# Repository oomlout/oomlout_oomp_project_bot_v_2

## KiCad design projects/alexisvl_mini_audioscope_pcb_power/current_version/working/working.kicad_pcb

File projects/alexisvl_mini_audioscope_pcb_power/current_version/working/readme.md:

# mini_audioscope
 
## summary 
* id: alexisvl_mini_audioscope_pcb_power
* user: alexisvl
* name: mini_audioscope
* board: pcb_power
* repo: https://github.com/alexisvl/mini-audioscope
* src_file_repo_kicad_pcb: pcb-power/pcb-power.kicad_pcb
* src_file_repo_kicad_pcb_link: https://github.com/alexisvl/mini-audioscope/tree/master/pcb-power/pcb-power.kicad_pcb

* src_file_repo_sch: pcb-power/pcb-power.sch
* src_file_repo_sch_link: https://github.com/alexisvl/mini-audioscope/tree/master/pcb-power/pcb-power.sch
* full details link: https://github.com/oomlout/oomlout_oomp_project_bot_v_2/tree/main/projects/alexisvl_mini_audioscope_pcb_power/current_version/working  

## schematic  
  
[schematic (pdf)](working_schematic.pdf) 

## pcb  

[board (pdf)](working.pdf)  

## working_bom
| Id | Designator | Footprint | Quantity | Designation | Supplier and ref |  | None | 
| --- | --- | --- | --- | --- | --- | --- | --- | 
| 1 | R2,R1 | R_Axial_DIN0309_L9.0mm_D3.2mm_P15.24mm_Horizontal | 2 | 330k/Â½W |  |  | [''] | 
| 2 | C11,C23,C24 | CP_Radial_D6.3mm_P2.50mm | 3 | 47u |  |  | [''] | 
| 3 | D10,D2,D4,D6,D3,D11,D7 | D_DO-41_SOD81_P10.16mm_Horizontal | 7 | UF4007 |  |  | [''] | 
| 4 | R8 | R_Axial_DIN0207_L6.3mm_D2.5mm_P10.16mm_Horizontal | 1 | 1k |  |  | [''] | 
| 5 | D12,D13 | D_DO-41_SOD81_P10.16mm_Horizontal | 2 | 1N4004 |  |  | [''] | 
| 6 | D5 | Diode_Bridge_Vishay_GBU | 1 | GBU4J |  |  | [''] | 
| 7 | TP3,TP5 | TestPoint_Loop_D2.60mm_Drill1.4mm_Beaded | 2 | GND |  |  | [''] | 
| 8 | C14,C19 | C_Rect_L26.5mm_W10.5mm_P22.50mm_MKS4 | 2 | 3u3/450 |  |  | [''] | 
| 9 | X14 | Pin_D1.1mm_L8.5mm_W2.5mm_FlatFork | 1 | +400V |  |  | [''] | 
| 10 | U3 | TO-220-3_Vertical | 1 | LM337 |  |  | [''] | 
| 11 | R15,R14 | R_Axial_DIN0309_L9.0mm_D3.2mm_P15.24mm_Horizontal | 2 | 220k/HW |  |  | [''] | 
| 12 | XT1.0 | Pin_D1.1mm_L8.5mm_W2.5mm_FlatFork | 1 | BLK |  |  | [''] | 
| 13 | XT1.9 | Pin_D1.1mm_L8.5mm_W2.5mm_FlatFork | 1 | WHT |  |  | [''] | 
| 14 | R16 | R_Axial_DIN0207_L6.3mm_D2.5mm_P10.16mm_Horizontal | 1 | 750 |  |  | [''] | 
| 15 | R17 | R_Axial_DIN0207_L6.3mm_D2.5mm_P10.16mm_Horizontal | 1 | 120 |  |  | [''] | 
| 16 | XT1.8 | Pin_D1.1mm_L8.5mm_W2.5mm_FlatFork | 1 | GRY |  |  | [''] | 
| 17 | X13 | Pin_D1.1mm_L8.5mm_W2.5mm_FlatFork | 1 | -9V |  |  | [''] | 
| 18 | R11 | R_Axial_DIN0309_L9.0mm_D3.2mm_P15.24mm_Horizontal | 1 | 270k/HW |  |  | [''] | 
| 19 | L1 | L_Toroid_Vertical_L33.0mm_W17.8mm_P12.70mm_Pulse_KM-5 | 1 | 150u/5A |  |  | [''] | 
| 20 | XT1.2 | Pin_D1.1mm_L8.5mm_W2.5mm_FlatFork | 1 | RED |  |  | [''] | 
| 21 | C12,C15,C22,C18,C16 | C_Rect_L18.0mm_W8.0mm_P15.00mm_FKS3_FKP3 | 5 | 1u/450 |  |  | [''] | 
| 22 | R10 | R_Axial_DIN0309_L9.0mm_D3.2mm_P12.70mm_Horizontal | 1 | 1k5/Â½W |  |  | [''] | 
| 23 | C6 | CP_Radial_D12.5mm_P5.00mm | 1 | 470u |  |  | [''] | 
| 24 | R7,R5 | R_Axial_DIN0207_L6.3mm_D2.5mm_P10.16mm_Horizontal | 2 | 3k3 |  |  | [''] | 
| 25 | XSW1 | Pin_D1.1mm_L8.5mm_W2.5mm_FlatFork | 1 | PH |  |  | [''] | 
| 26 | C17,C21 | CP_Radial_D8.0mm_P3.50mm | 2 | 220u |  |  | [''] | 
| 27 | D8,D9 | D_DO-41_SOD81_P10.16mm_Horizontal | 2 | 1N4007 |  |  | [''] | 
| 28 | XT1.4 | Pin_D1.1mm_L8.5mm_W2.5mm_FlatFork | 1 | YEL |  |  | [''] | 
| 29 | TP7 | TestPoint_Loop_D2.60mm_Drill1.4mm_Beaded | 1 | V-- |  |  | [''] | 
| 30 | HS1 | Heatsink_Fischer_SK104-STCB_35x13mm__2xDrill3.5mm_ScrewM3 | 1 | 513102B02500G |  |  | [''] | 
| 31 | RV1 | stock_pot | 1 | 500 |  |  | [''] | 
| 32 | X12 | Pin_D1.1mm_L8.5mm_W2.5mm_FlatFork | 1 | +9V |  |  | [''] | 
| 33 | FB1 | L_0805_2012Metric_Pad1.15x1.40mm_HandSolder | 1 | 742792023 |  |  | [''] | 
| 34 | C4 | C_Disc_D4.7mm_W2.5mm_P5.00mm | 1 | 4n7 |  |  | [''] | 
| 35 | C8,C7 | C_Rect_L18.0mm_W5.0mm_P15.00mm_FKS3_FKP3 | 2 | 47n/X2 |  |  | [''] | 
| 36 | XR1 | Pin_D1.1mm_L8.5mm_W2.5mm_FlatFork | 1 | H1 |  |  | [''] | 
| 37 | TP1 | TestPoint_Loop_D2.60mm_Drill1.4mm_Beaded | 1 | COMP |  |  | [''] | 
| 38 | XV1.14 | Pin_D1.1mm_L8.5mm_W2.5mm_FlatFork | 1 | H2 |  |  | [''] | 
| 39 | X15 | Pin_D1.1mm_L8.5mm_W2.5mm_FlatFork | 1 | -400V |  |  | [''] | 
| 40 | TP4 | TestPoint_Loop_D2.60mm_Drill1.4mm_Beaded | 1 | VSW |  |  | [''] | 
| 41 | R4 | R_Axial_DIN0207_L6.3mm_D2.5mm_P10.16mm_Horizontal | 1 | 10k |  |  | [''] | 
| 42 | XT1.1 | Pin_D1.1mm_L8.5mm_W2.5mm_FlatFork | 1 | BRN |  |  | [''] | 
| 43 | D1 | D_SOD-123 | 1 | MBR0540 |  |  | [''] | 
| 44 | R13 | R_Axial_DIN0309_L9.0mm_D3.2mm_P15.24mm_Horizontal | 1 | 680k/HW |  |  | [''] | 
| 45 | U2 | TO-220-3_Vertical | 1 | 7809 |  |  | [''] | 
| 46 | C3,C9 | C_Disc_D4.7mm_W2.5mm_P5.00mm | 2 | 100n |  |  | [''] | 
| 47 | R12 | R_Axial_DIN0414_L11.9mm_D4.5mm_P20.32mm_Horizontal | 1 | 3R9/1W |  |  | [''] | 
| 48 | XJ2.3 | Pin_D1.1mm_L8.5mm_W2.5mm_FlatFork | 1 | G |  |  | [''] | 
| 49 | C13 | C_Disc_D7.0mm_W2.5mm_P5.00mm | 1 | 100p/500V |  |  | [''] | 
| 50 | XT1.3 | Pin_D1.1mm_L8.5mm_W2.5mm_FlatFork | 1 | ORN |  |  | [''] | 
| 51 | U1 | DIP-8_W7.62mm_LongPads | 1 | UC3843 |  |  | [''] | 
| 52 | XJ2.2 | Pin_D1.1mm_L8.5mm_W2.5mm_FlatFork | 1 | N |  |  | [''] | 
| 53 | C2 | C_Disc_D4.7mm_W2.5mm_P5.00mm | 1 | 470p |  |  | [''] | 
| 54 | C10,C1 | C_Disc_D4.7mm_W2.5mm_P5.00mm | 2 | 100p |  |  | [''] | 
| 55 | C20 | CP_Radial_D18.0mm_P7.50mm | 1 | 3300u |  |  | [''] | 
| 56 | TH1 | C_Disc_D11.0mm_W5.0mm_P7.50mm | 1 | 60/800mA |  |  | [''] | 
| 57 | TP2 | TestPoint_Loop_D2.60mm_Drill1.4mm_Beaded | 1 | ISN |  |  | [''] | 
| 58 | R9 | R_2512_6332Metric_Pad1.52x3.35mm_HandSolder | 1 | 0R27/1W |  |  | [''] | 
| 59 | XT1.6 | Pin_D1.1mm_L8.5mm_W2.5mm_FlatFork | 1 | BLU |  |  | [''] | 
| 60 | C5 | C_Disc_D11.0mm_W5.0mm_P10.00mm | 1 | 2n2/Y2 |  |  | [''] | 
| 61 | NE1 | C_Radial_D8.0mm_H11.5mm_P3.50mm | 1 | A9A |  |  | [''] | 
| 62 | R6 | R_Axial_DIN0207_L6.3mm_D2.5mm_P10.16mm_Horizontal | 1 | 150k |  |  | [''] | 
| 63 | Q1 | SOT-223-3_TabPin2 | 1 | IPN70R1K5CE |  |  | [''] | 
| 64 | R3 | R_Axial_DIN0207_L6.3mm_D2.5mm_P10.16mm_Horizontal | 1 | 3k9 |  |  | [''] | 
| 65 | TP6 | TestPoint_Loop_D2.60mm_Drill1.4mm_Beaded | 1 | V++ |  |  | [''] | 

## bom_schematic
no data

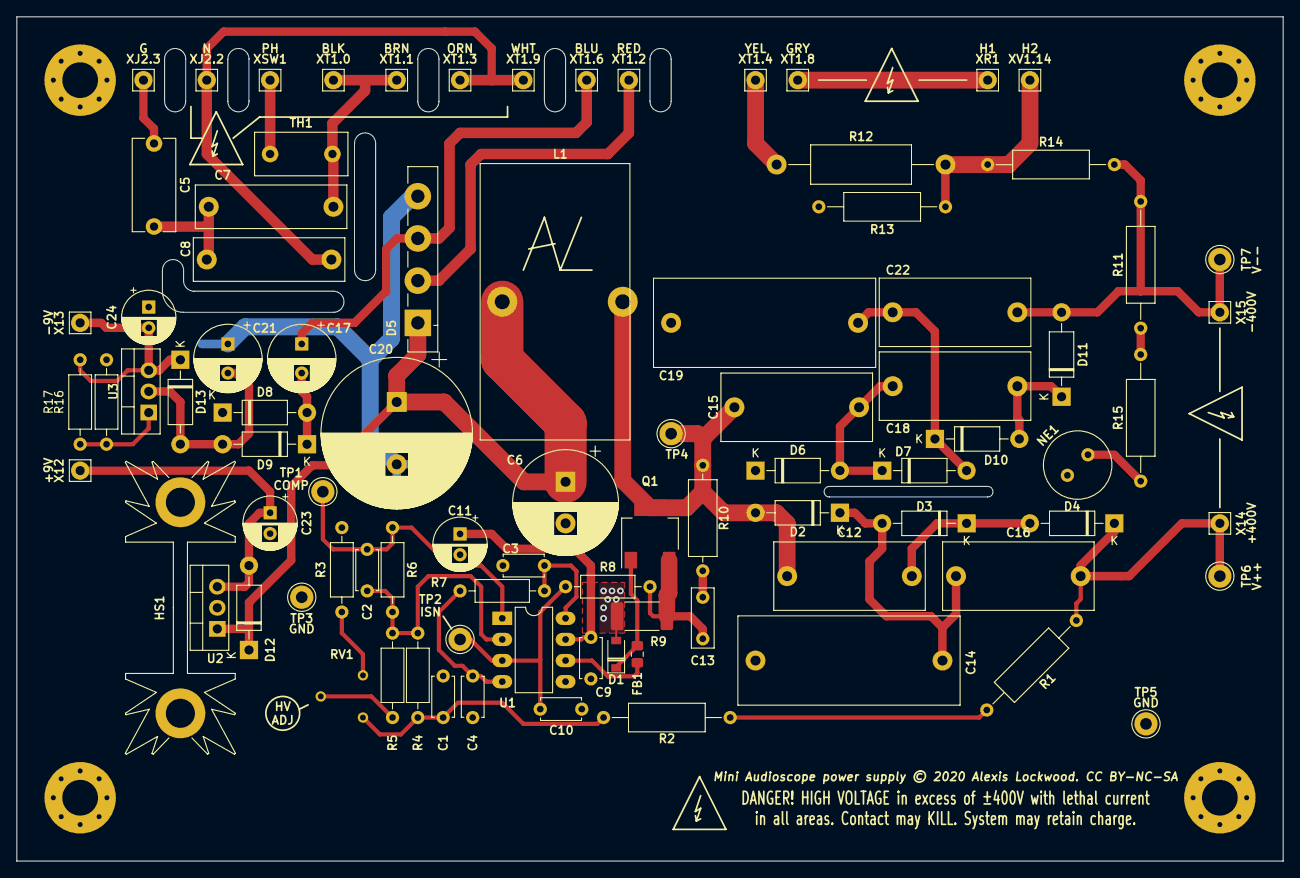
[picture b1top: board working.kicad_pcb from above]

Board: 2 copper layers, 152.4 x 101.6 mm, 92 parts (0 on the bottom side), 40 nets.

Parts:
C1, C10: 100p; C_Disc_D4.7mm_W2.5mm_P5.00mm
C2: 470p; C_Disc_D4.7mm_W2.5mm_P5.00mm
C3, C9: 100n; C_Disc_D4.7mm_W2.5mm_P5.00mm
C4: 4n7; C_Disc_D4.7mm_W2.5mm_P5.00mm
C5: 2n2/Y2; C_Disc_D11.0mm_W5.0mm_P10.00mm
C6: 470u; CP_Radial_D12.5mm_P5.00mm
C7, C8: 47n/X2; C_Rect_L18.0mm_W5.0mm_P15.00mm_FKS3_FKP3
C11, C23, C24: 47u; CP_Radial_D6.3mm_P2.50mm
C12, C15, C16, C18, C22: 1u/450; C_Rect_L18.0mm_W8.0mm_P15.00mm_FKS3_FKP3
C13: 100p/500V; C_Disc_D7.0mm_W2.5mm_P5.00mm
C14, C19: 3u3/450; C_Rect_L26.5mm_W10.5mm_P22.50mm_MKS4
C17, C21: 220u; CP_Radial_D8.0mm_P3.50mm
C20: 3300u; CP_Radial_D18.0mm_P7.50mm
D1: MBR0540; D_SOD-123
D2, D3, D4, D6, D7, D10, D11: UF4007; D_DO-41_SOD81_P10.16mm_Horizontal
D5: GBU4J; Diode_Bridge_Vishay_GBU
D8, D9: 1N4007; D_DO-41_SOD81_P10.16mm_Horizontal
D12, D13: 1N4004; D_DO-41_SOD81_P10.16mm_Horizontal
FB1: 742792023; L_0805_2012Metric_Pad1.15x1.40mm_HandSolder
H1, H2, H3, H4: GND; MountingHole_4.3mm_M4_Pad_Via
HS1: 513102B02500G; Heatsink_Fischer_SK104-STCB_35x13mm__2xDrill3.5mm_ScrewM3
L1: 150u/5A; L_Toroid_Vertical_L33.0mm_W17.8mm_P12.70mm_Pulse_KM-5
NE1: A9A; C_Radial_D8.0mm_H11.5mm_P3.50mm
Q1: IPN70R1K5CE; SOT-223-3_TabPin2
R1, R2: 330k/½W; R_Axial_DIN0309_L9.0mm_D3.2mm_P15.24mm_Horizontal
R3: 3k9; R_Axial_DIN0207_L6.3mm_D2.5mm_P10.16mm_Horizontal
R4: 10k; R_Axial_DIN0207_L6.3mm_D2.5mm_P10.16mm_Horizontal
R5, R7: 3k3; R_Axial_DIN0207_L6.3mm_D2.5mm_P10.16mm_Horizontal
R6: 150k; R_Axial_DIN0207_L6.3mm_D2.5mm_P10.16mm_Horizontal
R8: 1k; R_Axial_DIN0207_L6.3mm_D2.5mm_P10.16mm_Horizontal
R9: 0R27/1W; R_2512_6332Metric_Pad1.52x3.35mm_HandSolder
R10: 1k5/½W; R_Axial_DIN0309_L9.0mm_D3.2mm_P12.70mm_Horizontal
R11: 270k/HW; R_Axial_DIN0309_L9.0mm_D3.2mm_P15.24mm_Horizontal
R12: 3R9/1W; R_Axial_DIN0414_L11.9mm_D4.5mm_P20.32mm_Horizontal
R13: 680k/HW; R_Axial_DIN0309_L9.0mm_D3.2mm_P15.24mm_Horizontal
R14, R15: 220k/HW; R_Axial_DIN0309_L9.0mm_D3.2mm_P15.24mm_Horizontal
R16: 750; R_Axial_DIN0207_L6.3mm_D2.5mm_P10.16mm_Horizontal
R17: 120; R_Axial_DIN0207_L6.3mm_D2.5mm_P10.16mm_Horizontal
RV1: 500; stock_pot
TH1: 60/800mA; C_Disc_D11.0mm_W5.0mm_P7.50mm
TP1: COMP; TestPoint_Loop_D2.60mm_Drill1.4mm_Beaded
TP2: ISN; TestPoint_Loop_D2.60mm_Drill1.4mm_Beaded
TP3, TP5: GND; TestPoint_Loop_D2.60mm_Drill1.4mm_Beaded
TP4: VSW; TestPoint_Loop_D2.60mm_Drill1.4mm_Beaded
TP6: V++; TestPoint_Loop_D2.60mm_Drill1.4mm_Beaded
TP7: V--; TestPoint_Loop_D2.60mm_Drill1.4mm_Beaded
U1: UC3843; DIP-8_W7.62mm_LongPads
U2: 7809; TO-220-3_Vertical
U3: LM337; TO-220-3_Vertical
X12: +9V; Pin_D1.1mm_L8.5mm_W2.5mm_FlatFork
X13: -9V; Pin_D1.1mm_L8.5mm_W2.5mm_FlatFork
X14: +400V; Pin_D1.1mm_L8.5mm_W2.5mm_FlatFork
X15: -400V; Pin_D1.1mm_L8.5mm_W2.5mm_FlatFork
XJ2.2: N; Pin_D1.1mm_L8.5mm_W2.5mm_FlatFork
XJ2.3: G; Pin_D1.1mm_L8.5mm_W2.5mm_FlatFork
XR1: H1; Pin_D1.1mm_L8.5mm_W2.5mm_FlatFork
XSW1: PH; Pin_D1.1mm_L8.5mm_W2.5mm_FlatFork
XT1.0: BLK; Pin_D1.1mm_L8.5mm_W2.5mm_FlatFork
XT1.1: BRN; Pin_D1.1mm_L8.5mm_W2.5mm_FlatFork
XT1.2: RED; Pin_D1.1mm_L8.5mm_W2.5mm_FlatFork
XT1.3: ORN; Pin_D1.1mm_L8.5mm_W2.5mm_FlatFork
XT1.4: YEL; Pin_D1.1mm_L8.5mm_W2.5mm_FlatFork
XT1.6: BLU; Pin_D1.1mm_L8.5mm_W2.5mm_FlatFork
XT1.8: GRY; Pin_D1.1mm_L8.5mm_W2.5mm_FlatFork
XT1.9: WHT; Pin_D1.1mm_L8.5mm_W2.5mm_FlatFork
XV1.14: H2; Pin_D1.1mm_L8.5mm_W2.5mm_FlatFork

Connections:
+9V: C9.1, C11.1, U1.7
+15UNREG: C6.1, C20.1, D5.1, D12.1, L1.1, U2.1
/+400V: C16.2, D4.1, R1.1, TP6.1, X14.1
/-400V: C22.2, D11.2, R11.2, R14.2, TP7.1, X15.1
/H1: XR1.1, XT1.8.1
/H2: R12.1, XT1.4.1
/H2_2: R12.2, R13.1, R14.1, XV1.14.1
/HALFFB_250: R1.2, R2.2
/LINE: TH1.1, XSW1.1
/LINE_NTC: C7.1, TH1.2, XT1.0.1, XT1.1.1
/MULT1_400: C12.2, D3.1, D4.2
/MULT2_250: C14.2, C16.1, D2.1, D3.2
/MULT3_400: C18.2, D10.2, D11.1
/MULT4_250: C19.2, C22.1, D7.2, D10.1
/MULT5_250: C15.2, C18.1, D6.2, D7.1
/NEON_250: R11.1, R15.2
/NEUT: C8.2, XJ2.2.1, XT1.3.1, XT1.9.1
/SNUB: C13.2, R10.2
/VSW: C12.1, C15.1, D2.2, L1.2, Q1.2, R10.1, TP4.1
/X2_CENT: C5.2, C7.2, C8.1
GND: C1.2, C3.2, C4.2, C5.1, C6.2, C9.2, C10.2, C11.2, C14.1, C19.1, C20.2, C21.1, C23.2, C24.1, D1.2, D5.4, D6.1, D8.1, H1.1, H2.1, H3.1, H4.1, HS1.1, NE1.2, R3.1, R9.2, R13.2, R16.1, TP3.1, TP5.1, U1.5, U2.2, XJ2.3.1
unnamed: C1.1, R2.1, R4.2, RV1.1
unnamed: C2.1, R4.1, R5.1, R6.2, U1.2
unnamed: C2.2, R6.1, TP1.1, U1.1
unnamed: C3.1, R7.1, U1.8
unnamed: C4.1, R7.2, U1.4
unnamed: C10.1, R8.1, TP2.1, U1.3
unnamed: C13.1, Q1.3, R8.2, R9.1
unnamed: C17.1, D5.3, XT1.6.1
unnamed: C17.2, D8.2, D9.1
unnamed: C21.2, D9.2, D13.2, U3.2
unnamed: C23.1, D12.2, U2.3, X12.1
unnamed: C24.2, D13.1, R17.1, U3.3, X13.1
unnamed: D1.1, FB1.2, Q1.1
unnamed: D5.2, XT1.2.1
unnamed: FB1.1, U1.6
unnamed: NE1.1, R15.1
unnamed: R3.2, RV1.3
unnamed: R5.2, RV1.2
unnamed: R16.2, R17.2, U3.1

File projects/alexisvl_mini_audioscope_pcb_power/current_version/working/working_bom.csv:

"Id";"Designator";"Footprint";"Quantity";"Designation";"Supplier and ref";
1;"R2,R1";"R_Axial_DIN0309_L9.0mm_D3.2mm_P15.24mm_Horizontal";2;"330k/½W";;;
2;"C11,C23,C24";"CP_Radial_D6.3mm_P2.50mm";3;"47u";;;
3;"D10,D2,D4,D6,D3,D11,D7";"D_DO-41_SOD81_P10.16mm_Horizontal";7;"UF4007";;;
4;"R8";"R_Axial_DIN0207_L6.3mm_D2.5mm_P10.16mm_Horizontal";1;"1k";;;
5;"D12,D13";"D_DO-41_SOD81_P10.16mm_Horizontal";2;"1N4004";;;
6;"D5";"Diode_Bridge_Vishay_GBU";1;"GBU4J";;;
7;"TP3,TP5";"TestPoint_Loop_D2.60mm_Drill1.4mm_Beaded";2;"GND";;;
8;"C14,C19";"C_Rect_L26.5mm_W10.5mm_P22.50mm_MKS4";2;"3u3/450";;;
9;"X14";"Pin_D1.1mm_L8.5mm_W2.5mm_FlatFork";1;"+400V";;;
10;"U3";"TO-220-3_Vertical";1;"LM337";;;
11;"R15,R14";"R_Axial_DIN0309_L9.0mm_D3.2mm_P15.24mm_Horizontal";2;"220k/HW";;;
12;"XT1.0";"Pin_D1.1mm_L8.5mm_W2.5mm_FlatFork";1;"BLK";;;
13;"XT1.9";"Pin_D1.1mm_L8.5mm_W2.5mm_FlatFork";1;"WHT";;;
14;"R16";"R_Axial_DIN0207_L6.3mm_D2.5mm_P10.16mm_Horizontal";1;"750";;;
15;"R17";"R_Axial_DIN0207_L6.3mm_D2.5mm_P10.16mm_Horizontal";1;"120";;;
16;"XT1.8";"Pin_D1.1mm_L8.5mm_W2.5mm_FlatFork";1;"GRY";;;
17;"X13";"Pin_D1.1mm_L8.5mm_W2.5mm_FlatFork";1;"-9V";;;
18;"R11";"R_Axial_DIN0309_L9.0mm_D3.2mm_P15.24mm_Horizontal";1;"270k/HW";;;
19;"L1";"L_Toroid_Vertical_L33.0mm_W17.8mm_P12.70mm_Pulse_KM-5";1;"150u/5A";;;
20;"XT1.2";"Pin_D1.1mm_L8.5mm_W2.5mm_FlatFork";1;"RED";;;
21;"C12,C15,C22,C18,C16";"C_Rect_L18.0mm_W8.0mm_P15.00mm_FKS3_FKP3";5;"1u/450";;;
22;"R10";"R_Axial_DIN0309_L9.0mm_D3.2mm_P12.70mm_Horizontal";1;"1k5/½W";;;
23;"C6";"CP_Radial_D12.5mm_P5.00mm";1;"470u";;;
24;"R7,R5";"R_Axial_DIN0207_L6.3mm_D2.5mm_P10.16mm_Horizontal";2;"3k3";;;
25;"XSW1";"Pin_D1.1mm_L8.5mm_W2.5mm_FlatFork";1;"PH";;;
26;"C17,C21";"CP_Radial_D8.0mm_P3.50mm";2;"220u";;;
27;"D8,D9";"D_DO-41_SOD81_P10.16mm_Horizontal";2;"1N4007";;;
28;"XT1.4";"Pin_D1.1mm_L8.5mm_W2.5mm_FlatFork";1;"YEL";;;
29;"TP7";"TestPoint_Loop_D2.60mm_Drill1.4mm_Beaded";1;"V--";;;
30;"HS1";"Heatsink_Fischer_SK104-STCB_35x13mm__2xDrill3.5mm_ScrewM3";1;"513102B02500G";;;
31;"RV1";"stock_pot";1;"500";;;
32;"X12";"Pin_D1.1mm_L8.5mm_W2.5mm_FlatFork";1;"+9V";;;
33;"FB1";"L_0805_2012Metric_Pad1.15x1.40mm_HandSolder";1;"742792023";;;
34;"C4";"C_Disc_D4.7mm_W2.5mm_P5.00mm";1;"4n7";;;
35;"C8,C7";"C_Rect_L18.0mm_W5.0mm_P15.00mm_FKS3_FKP3";2;"47n/X2";;;
36;"XR1";"Pin_D1.1mm_L8.5mm_W2.5mm_FlatFork";1;"H1";;;
37;"TP1";"TestPoint_Loop_D2.60mm_Drill1.4mm_Beaded";1;"COMP";;;
38;"XV1.14";"Pin_D1.1mm_L8.5mm_W2.5mm_FlatFork";1;"H2";;;
39;"X15";"Pin_D1.1mm_L8.5mm_W2.5mm_FlatFork";1;"-400V";;;
40;"TP4";"TestPoint_Loop_D2.60mm_Drill1.4mm_Beaded";1;"VSW";;;
41;"R4";"R_Axial_DIN0207_L6.3mm_D2.5mm_P10.16mm_Horizontal";1;"10k";;;
42;"XT1.1";"Pin_D1.1mm_L8.5mm_W2.5mm_FlatFork";1;"BRN";;;
43;"D1";"D_SOD-123";1;"MBR0540";;;
44;"R13";"R_Axial_DIN0309_L9.0mm_D3.2mm_P15.24mm_Horizontal";1;"680k/HW";;;
45;"U2";"TO-220-3_Vertical";1;"7809";;;
46;"C3,C9";"C_Disc_D4.7mm_W2.5mm_P5.00mm";2;"100n";;;
47;"R12";"R_Axial_DIN0414_L11.9mm_D4.5mm_P20.32mm_Horizontal";1;"3R9/1W";;;
48;"XJ2.3";"Pin_D1.1mm_L8.5mm_W2.5mm_FlatFork";1;"G";;;
49;"C13";"C_Disc_D7.0mm_W2.5mm_P5.00mm";1;"100p/500V";;;
50;"XT1.3";"Pin_D1.1mm_L8.5mm_W2.5mm_FlatFork";1;"ORN";;;
51;"U1";"DIP-8_W7.62mm_LongPads";1;"UC3843";;;
52;"XJ2.2";"Pin_D1.1mm_L8.5mm_W2.5mm_FlatFork";1;"N";;;
53;"C2";"C_Disc_D4.7mm_W2.5mm_P5.00mm";1;"470p";;;
54;"C10,C1";"C_Disc_D4.7mm_W2.5mm_P5.00mm";2;"100p";;;
55;"C20";"CP_Radial_D18.0mm_P7.50mm";1;"3300u";;;
56;"TH1";"C_Disc_D11.0mm_W5.0mm_P7.50mm";1;"60/800mA";;;
57;"TP2";"TestPoint_Loop_D2.60mm_Drill1.4mm_Beaded";1;"ISN";;;
58;"R9";"R_2512_6332Metric_Pad1.52x3.35mm_HandSolder";1;"0R27/1W";;;
59;"XT1.6";"Pin_D1.1mm_L8.5mm_W2.5mm_FlatFork";1;"BLU";;;
60;"C5";"C_Disc_D11.0mm_W5.0mm_P10.00mm";1;"2n2/Y2";;;
61;"NE1";"C_Radial_D8.0mm_H11.5mm_P3.50mm";1;"A9A";;;
62;"R6";"R_Axial_DIN0207_L6.3mm_D2.5mm_P10.16mm_Horizontal";1;"150k";;;
63;"Q1";"SOT-223-3_TabPin2";1;"IPN70R1K5CE";;;
64;"R3";"R_Axial_DIN0207_L6.3mm_D2.5mm_P10.16mm_Horizontal";1;"3k9";;;
65;"TP6";"TestPoint_Loop_D2.60mm_Drill1.4mm_Beaded";1;"V++";;;

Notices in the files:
projects/alexisvl_mini_audioscope_pcb_power/current_version/working/working.kicad_pcb:
Mini Audioscope power supply © 2020 Alexis Lockwood. CC BY-NC-SA
